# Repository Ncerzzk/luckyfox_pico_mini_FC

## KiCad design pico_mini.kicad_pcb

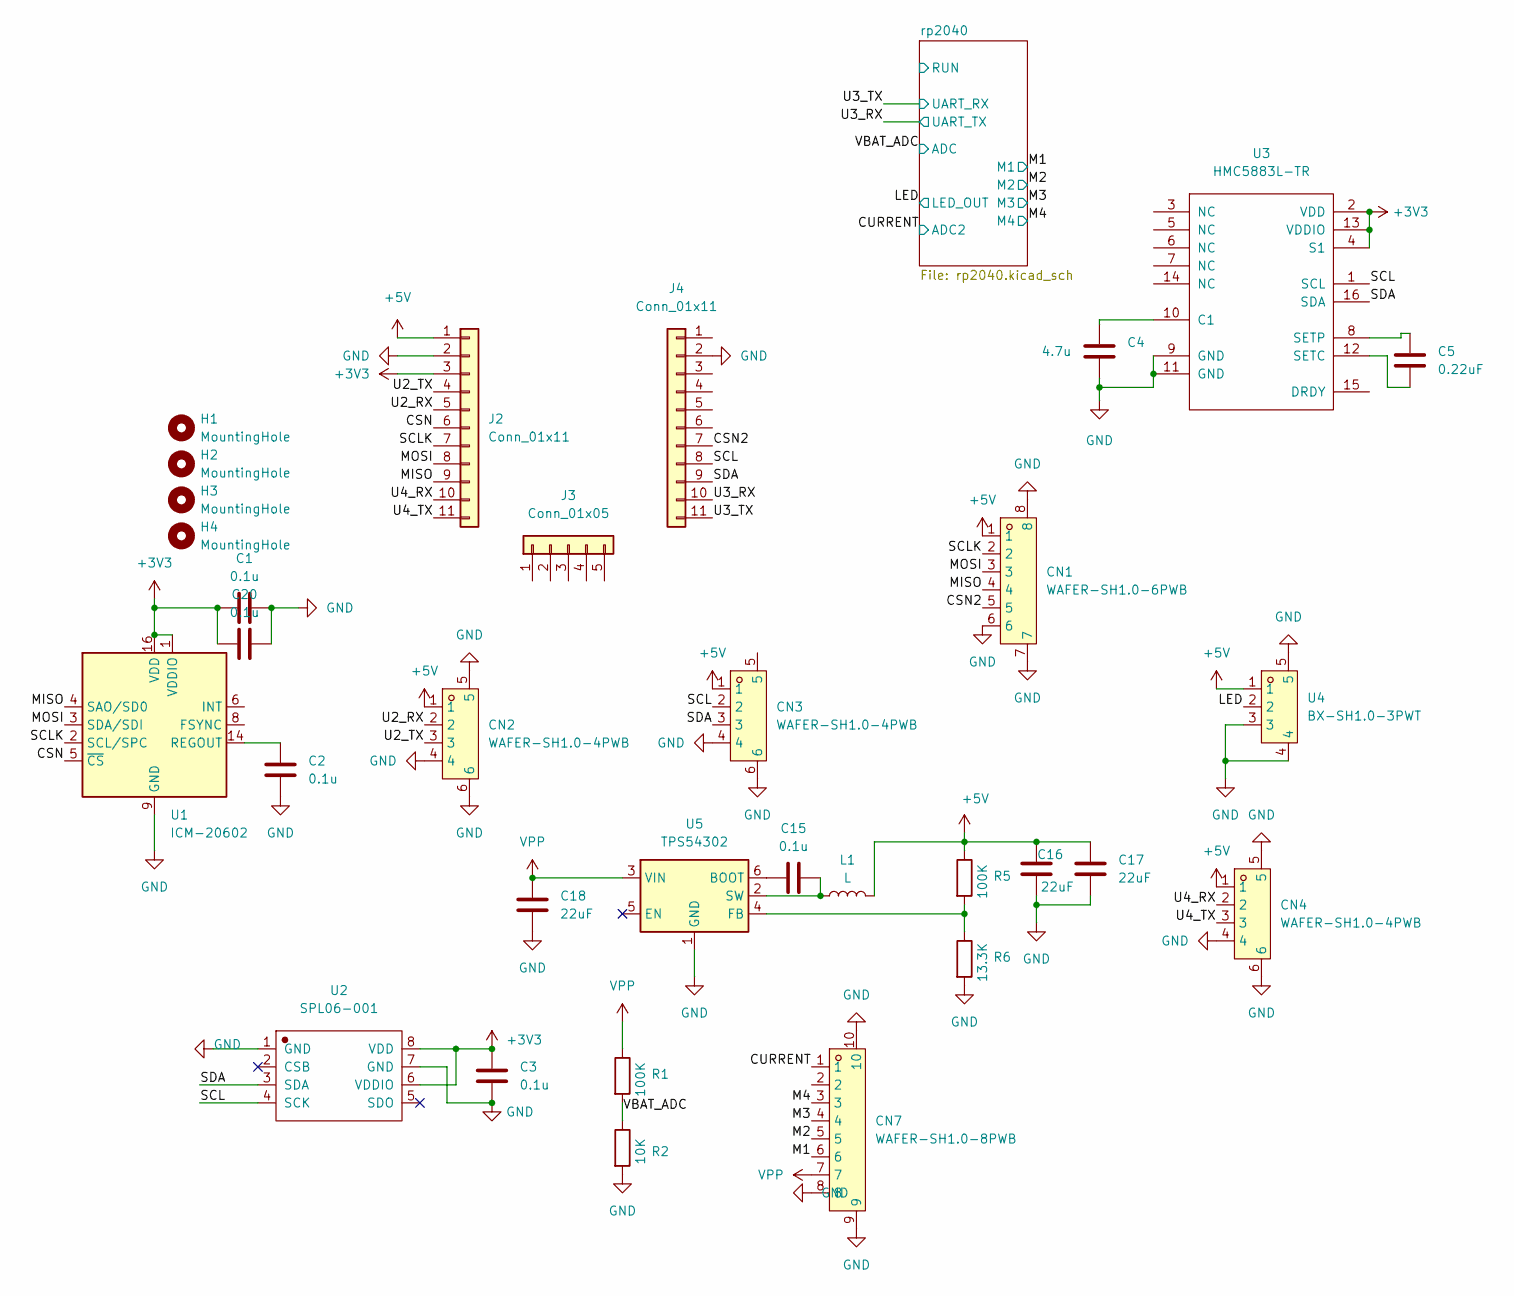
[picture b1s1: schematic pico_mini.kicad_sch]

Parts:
C1, C2, C3, C15, C20: 0.1u; C_0402_1005Metric
C4: 4.7u; C_0402_1005Metric
C5: 0.22uF; C_0402_1005Metric
C16, C17, C18: 22uF; C_0603_1608Metric
CN1: WAFER-SH1.0-6PWB; CONN-SMD_6P-P1.00_XUNPU_WAFER-SH1.0-6PWB; LCSC Part C3029345
CN2, CN3, CN4: WAFER-SH1.0-4PWB; CONN-SMD_4P-P1.00_WAFER-SH1.0-4PWB; LCSC Part C3029343
CN7: WAFER-SH1.0-8PWB; CONN-SMD_8P-P1.00_XUNPU_WAFER-SH1.0-8PWB; LCSC Part C3029347
H1, H2, H3, H4: MountingHole; MountingHole_3.2mm_M3
J2, J4: Conn_01x11; PinHeader_1x11_P2.54mm_Vertical
J3: Conn_01x05
L1: L; L_Wuerth_HCI-5040
R1, R5: 100K; C_0402_1005Metric; LCSC C274349
R2: 10K; C_0402_1005Metric; LCSC C274349
R6: 13.3K; C_0402_1005Metric; LCSC C274349
U1: ICM-20602; LGA-16_3x3mm_P0.5mm_LayoutBorder3x5y
U2: SPL06-001; Bosch_LGA-8_2x2.5mm_P0.65mm_ClockwisePinNumbering
U3: HMC5883L-TR; LGA-16_3x3mm_P0.5mm
U4: BX-SH1.0-3PWT; CONN-SMD_3P-P1.00_BX-SH1.0-3PWT; LCSC Part C18077909
U5: TPS54302; SOT-23-6

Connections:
+3V3: C1.2, C3.1, C20.2, J2.3, U1.1 (VDDIO), U1.16 (VDD), U2.6 (VDDIO), U2.8 (VDD), U3.2 (VDD), U3.4 (S1), U3.13 (VDDIO); also elsewhere on the board
+5V: C16.1, C17.1, CN1.1, CN2.1, CN3.1, CN4.1, J2.1, L1.2, R5.1, U4.1; also elsewhere on the board
/CSN: J2.6, U1.5 (~CS)
/CSN2: CN1.5, J4.7
/CURRENT: CN7.1; also elsewhere on the board
/LED: U4.2; also elsewhere on the board
/M1: CN7.6; also elsewhere on the board
/M2: CN7.5; also elsewhere on the board
/M3: CN7.4; also elsewhere on the board
/M4: CN7.3; also elsewhere on the board
/MISO: CN1.4, J2.9, U1.4 (SAO/SD0)
/MOSI: CN1.3, J2.8, U1.3 (SDA/SDI)
/SCL: CN3.2, J4.8, U2.4 (SCK), U3.1 (SCL)
/SCLK: CN1.2, J2.7, U1.2 (SCL/SPC)
/SDA: CN3.3, J4.9, U2.3 (SDA), U3.16 (SDA)
/U2_RX: CN2.2, J2.5
/U2_TX: CN2.3, J2.4
/U3_RX: J4.10; also elsewhere on the board
/U3_TX: J4.11; also elsewhere on the board
/U4_RX: CN4.2, J2.10
/U4_TX: CN4.3, J2.11
/VBAT_ADC: R1.2, R2.1; also elsewhere on the board
GND: C1.1, C2.2, C3.2, C4.2, C16.2, C17.2, C18.2, C20.1, CN1.6, CN1.7, CN1.8, CN2.4, CN2.5, CN2.6, CN3.4, CN3.6, CN4.4, CN4.5, CN4.6, CN7.8, CN7.9, CN7.10, J2.2, J4.2, R2.2, R6.2, U1.9 (GND), U1.10 (GND), U1.11 (GND), U1.12 (GND), U1.13 (GND), U1.15 (GND), U2.1 (GND), U2.7 (GND), U3.9 (GND), U3.11 (GND), U4.3, U4.4, U4.5, U5.1 (GND); also elsewhere on the board
unnamed: C2.1, U1.14 (REGOUT)
unnamed: C4.1, U3.10 (C1)
unnamed: C5.2, U3.12 (SETC)
unnamed: C5.1, U3.8 (SETP)
unnamed: C15.2, U5.6 (BOOT)
unnamed: R5.2, R6.1, U5.4 (FB)
unnamed: C15.1, L1.1, U5.2 (SW)
VPP: C18.1, CN7.7, R1.1, U5.3 (VIN)

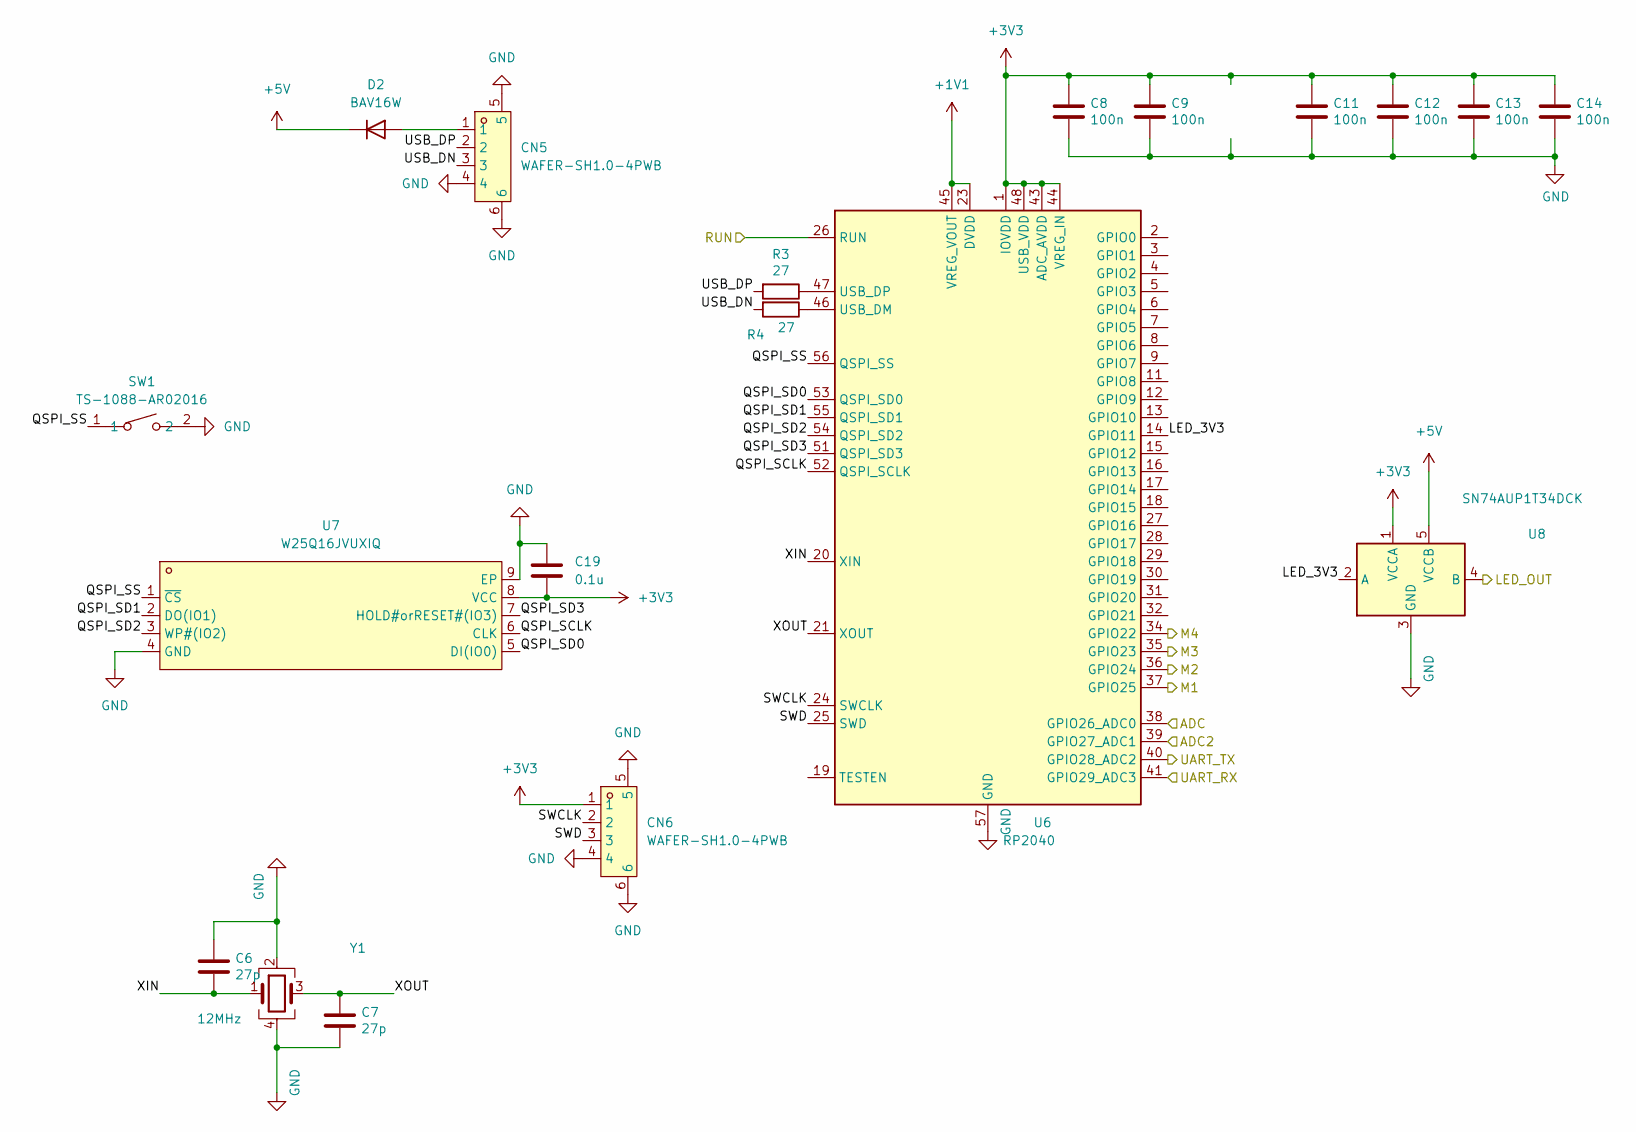
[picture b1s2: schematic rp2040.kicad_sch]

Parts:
C6, C7: 27p; C_0402_1005Metric; LCSC C52923
C8, C9, C11, C12, C13, C14: 100n; C_0402_1005Metric; LCSC C126504
C19: 0.1u; C_0402_1005Metric
CN5, CN6: WAFER-SH1.0-4PWB; CONN-SMD_4P-P1.00_WAFER-SH1.0-4PWB; LCSC Part C3029343
D2: BAV16W; D_SOD-123
R3, R4: 27; C_0402_1005Metric; LCSC C274349
SW1: TS-1088-AR02016; SW-SMD_L3.9-W3.0-P4.45; LCSC Part C720477
U6: RP2040; QFN-56-1EP_7x7mm_P0.4mm_EP3.2x3.2mm
U7: W25Q16JVUXIQ; USON-8_L3.0-W2.0-P0.50-BL-EP; LCSC Part C2843335
U8: SN74AUP1T34DCK; SOT-353_SC-70-5
Y1: 12MHz; Crystal_SMD_2520-4Pin_2.5x2.0mm

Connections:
+1V1: U6.23 (DVDD), U6.45 (VREG_VOUT), U6.50 (DVDD)
+3V3: C8.1, C9.1, C11.1, C12.1, C13.1, C14.1, C19.2, CN6.1, U6.1 (IOVDD), U6.10 (IOVDD), U6.22 (IOVDD), U6.33 (IOVDD), U6.42 (IOVDD), U6.43 (ADC_AVDD), U6.44 (VREG_IN), U6.48 (USB_VDD), U6.49 (IOVDD), U7.8 (VCC), U8.1 (VCCA); also elsewhere on the board
+5V: D2.1 (K), U8.5 (VCCB); also elsewhere on the board
/CURRENT: U6.39 (GPIO27_ADC1); also elsewhere on the board
/LED: U8.4 (B); also elsewhere on the board
/M1: U6.37 (GPIO25); also elsewhere on the board
/M2: U6.36 (GPIO24); also elsewhere on the board
/M3: U6.35 (GPIO23); also elsewhere on the board
/M4: U6.34 (GPIO22); also elsewhere on the board
/U3_RX: U6.40 (GPIO28_ADC2); also elsewhere on the board
/U3_TX: U6.41 (GPIO29_ADC3); also elsewhere on the board
/VBAT_ADC: U6.38 (GPIO26_ADC0); also elsewhere on the board
/rp2040/LED_3V3: U6.14 (GPIO11), U8.2 (A)
/rp2040/QSPI_SCLK: U6.52 (QSPI_SCLK), U7.6 (CLK)
/rp2040/QSPI_SD0: U6.53 (QSPI_SD0), U7.5 (DI(IO0))
/rp2040/QSPI_SD1: U6.55 (QSPI_SD1), U7.2 (DO(IO1))
/rp2040/QSPI_SD2: U6.54 (QSPI_SD2), U7.3 (WP#(IO2))
/rp2040/QSPI_SD3: U6.51 (QSPI_SD3), U7.7 (HOLD#orRESET#(IO3))
/rp2040/QSPI_SS: SW1.1, U6.56 (QSPI_SS), U7.1 (~CS)
/rp2040/RUN: U6.26 (RUN)
/rp2040/SWCLK: CN6.2, U6.24 (SWCLK)
/rp2040/SWD: CN6.3, U6.25 (SWD)
/rp2040/USB_DN: CN5.3, R4.2
/rp2040/USB_DP: CN5.2, R3.2
/rp2040/XIN: C6.2, U6.20 (XIN), Y1.1
/rp2040/XOUT: C7.1, U6.21 (XOUT), Y1.3
GND: C6.1, C7.2, C8.2, C9.2, C11.2, C12.2, C13.2, C14.2, C19.1, CN5.4, CN5.5, CN5.6, CN6.4, CN6.5, CN6.6, SW1.2, U6.57 (GND), U7.4 (GND), U7.9 (EP), U8.3 (GND), Y1.2, Y1.4; also elsewhere on the board
unnamed: CN5.1, D2.2 (A)
unnamed: R4.1, U6.46 (USB_DM)
unnamed: R3.1, U6.47 (USB_DP)

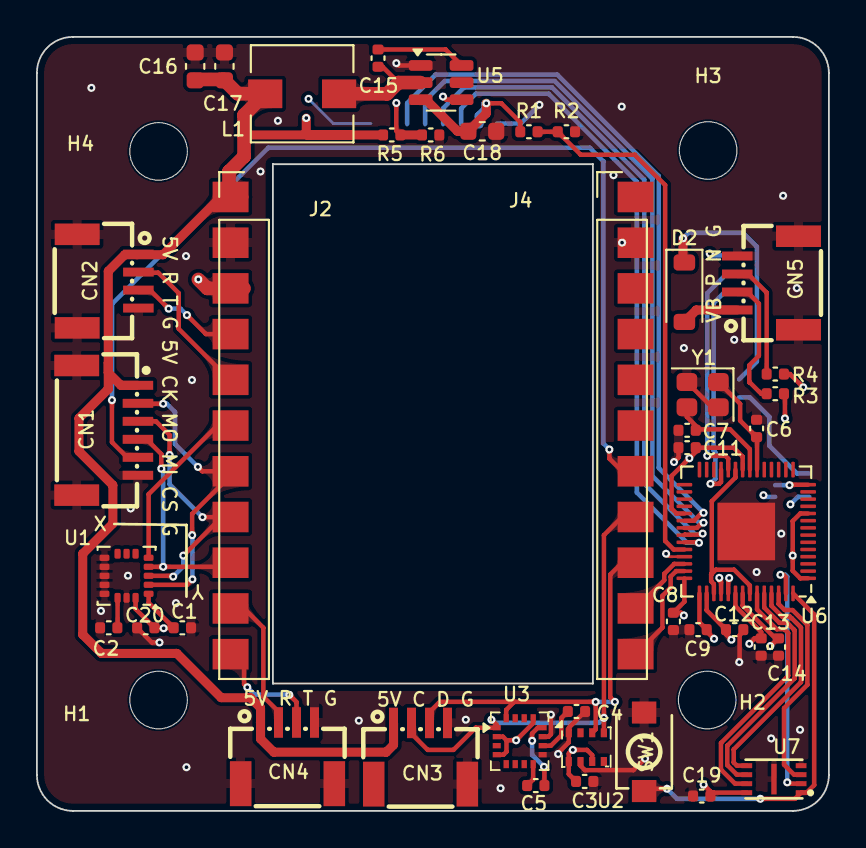
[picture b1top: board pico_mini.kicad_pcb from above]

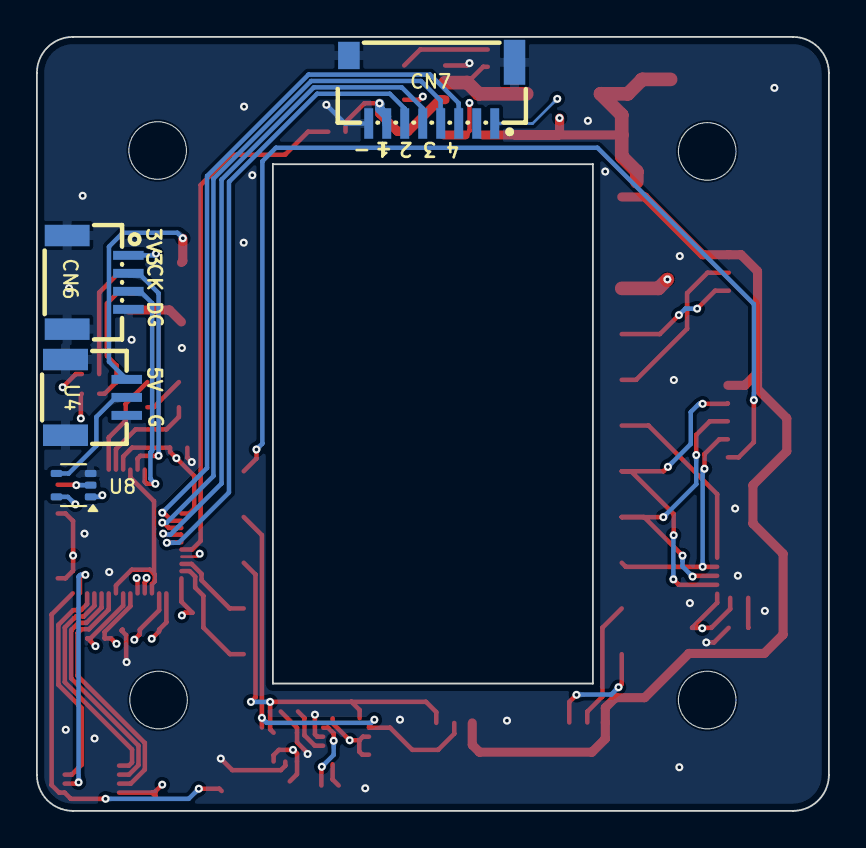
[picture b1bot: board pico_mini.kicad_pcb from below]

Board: 4 copper layers, 44.0 x 43.0 mm, 50 parts (4 on the bottom side), 48 nets.

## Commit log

2025-05-11 init
